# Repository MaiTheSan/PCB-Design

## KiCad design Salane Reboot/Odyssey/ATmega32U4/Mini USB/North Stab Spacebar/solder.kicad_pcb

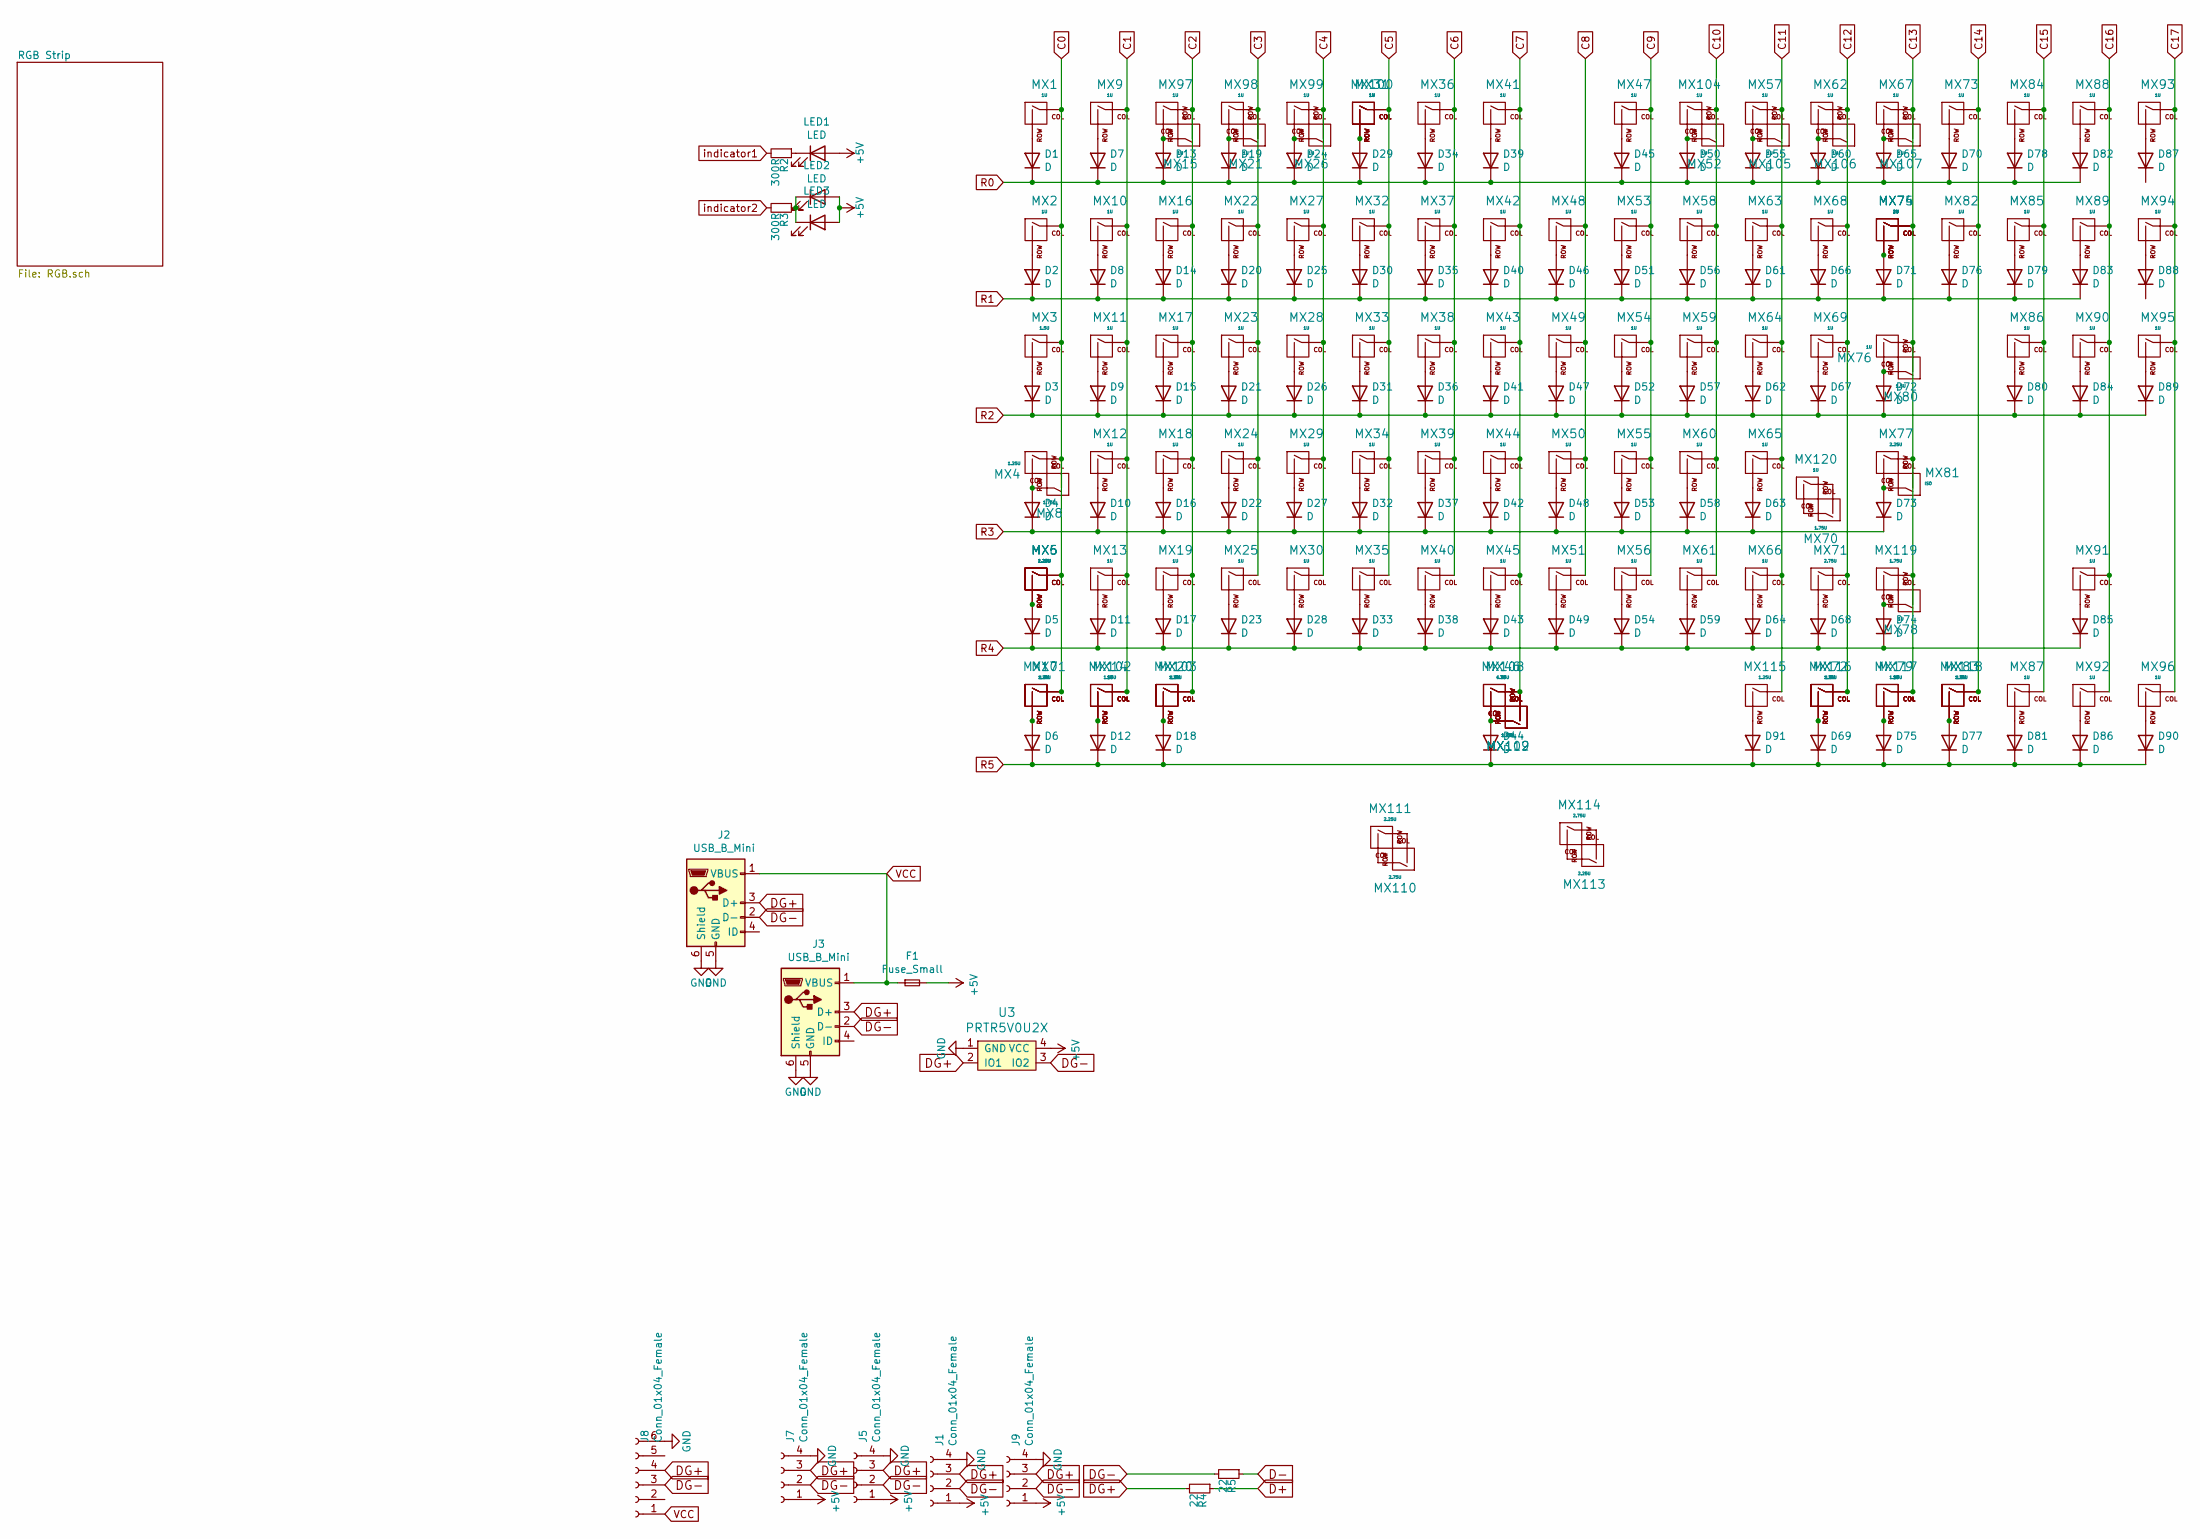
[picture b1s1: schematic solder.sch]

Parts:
D1, D2, D3, D4, D5, D6, D7, D8, D9, D10, D11, D12, D13, D14, D15, D16, D17, D18, D19, D20, D21, D22, D23, D24, D25, D26, D27, D28, D29, D30, D31, D32, D33, D34, D35, D36, D37, D38, D39, D40, D41, D42, D43, D44, D45, D46, D47, D48, D49, D50, D51, D52, D53, D54, D55, D56, D57, D58, D59, D60, D61, D62, D63, D64, D65, D66, D67, D68, D69, D70, D71, D72, D73, D74, D75, D76, D77, D78, D79, D80, D81, D82, D83, D84, D85, D86, D87, D88, D89, D90, D91: D; DIODE_1206_SawnsProjects
F1: Fuse_Small; Fuse_SMD1206_Reflow
J1, J7, J9: Conn_01x04_Female; JST-SR-4
J2, J3: USB_B_Mini; Molex-0548190589
J5: Conn_01x04_Female; PinHeader_1x04_P1.27mm_Vertical
J8: Conn_01x04_Female; BreakoutUSB
LED1, LED3: LED; MXOnly-LEDONLY-FLIPPED
LED2: LED; MXOnly-LEDONLY
MX1, MX2, MX9, MX10, MX11, MX12, MX13, MX14, MX15, MX16, MX17, MX18, MX19, MX21, MX22, MX23, MX24, MX25, MX26, MX27, MX28, MX29, MX30, MX31, MX32, MX33, MX34, MX35, MX36, MX37, MX38, MX39, MX40, MX41, MX42, MX43, MX44, MX45, MX47, MX48, MX49, MX50, MX51, MX52, MX53, MX54, MX55, MX56, MX57, MX58, MX59, MX60, MX61, MX62, MX63, MX64, MX65, MX66, MX67, MX68, MX69, MX73, MX74, MX76, MX78, MX79, MX82, MX84, MX85, MX86, MX87, MX88, MX89, MX90, MX91, MX92, MX93, MX94, MX95, MX96, MX97, MX98, MX99, MX100, MX104, MX105, MX106, MX107, MX120: 1U; MXOnly-1U-NoLED
MX3, MX7, MX20, MX72, MX80, MX83: 1.5U; MXOnly-1.5U-NoLED
MX4, MX5, MX101, MX102, MX103, MX109, MX112, MX115, MX116, MX117, MX118: 1.25U; MXOnly-1.25U-NoLED
MX6: 2.25U; MXOnly-2.25U-NoLED
MX8, MX70, MX119: 1.75U; MXOnly-1.75U-NoLED
MX46: 7U; MXOnly-7U-ReversedStabilizers-NoLED
MX71: 2.75U; MXOnly-2.75U-NoLED
MX75: 2U; MXOnly-2U-NoLED
MX77, MX111, MX113: 2.25U; MXOnly-2.25U-ReversedStabilizers-NoLED
MX81: ISO; MXOnly-ISO-ROTATED-ReversedStabilizers-NoLED
MX108: 6.25U; MXOnly-6.25U-ReversedStabilizers-NoLED
MX110, MX114: 2.75U; MXOnly-2.75U-ReversedStabilizers-NoLED
R2, R3: 300R; R_0805
R4, R5: 22; R_0805
U3: PRTR5V0U2X; SOT143B

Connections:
+5V: F1.2, J1.1, J5.1, J7.1, J9.1, LED1.2 (A), LED2.2 (A), LED3.2 (A), U3.4 (VCC)
C0: MX1.1 (COL), MX2.1 (COL), MX3.1 (COL), MX4.1 (COL), MX5.1 (COL), MX6.1 (COL), MX7.1 (COL), MX8.2 (ROW), MX101.1 (COL)
C1: MX9.1 (COL), MX10.1 (COL), MX11.1 (COL), MX12.1 (COL), MX13.1 (COL), MX14.1 (COL), MX102.1 (COL)
C2: MX15.2 (ROW), MX16.1 (COL), MX17.1 (COL), MX18.1 (COL), MX19.1 (COL), MX20.1 (COL), MX97.1 (COL), MX103.1 (COL)
C3: MX21.2 (ROW), MX22.1 (COL), MX23.1 (COL), MX24.1 (COL), MX25.1 (COL), MX98.1 (COL)
C4: MX26.2 (ROW), MX27.1 (COL), MX28.1 (COL), MX29.1 (COL), MX30.1 (COL), MX99.1 (COL)
C5: MX31.1 (COL), MX32.1 (COL), MX33.1 (COL), MX34.1 (COL), MX35.1 (COL), MX100.1 (COL)
C6: MX36.1 (COL), MX37.1 (COL), MX38.1 (COL), MX39.1 (COL), MX40.1 (COL)
C7: MX41.1 (COL), MX42.1 (COL), MX43.1 (COL), MX44.1 (COL), MX45.1 (COL), MX46.1 (COL), MX108.1 (COL), MX109.2 (ROW), MX112.2 (ROW)
C8: MX48.1 (COL), MX49.1 (COL), MX50.1 (COL), MX51.1 (COL)
C9: MX47.1 (COL), MX53.1 (COL), MX54.1 (COL), MX55.1 (COL), MX56.1 (COL)
C10: MX52.2 (ROW), MX58.1 (COL), MX59.1 (COL), MX60.1 (COL), MX61.1 (COL), MX104.1 (COL)
C11: MX57.1 (COL), MX63.1 (COL), MX64.1 (COL), MX65.1 (COL), MX66.1 (COL), MX105.2 (ROW), MX115.1 (COL)
C12: MX62.1 (COL), MX68.1 (COL), MX69.1 (COL), MX71.1 (COL), MX72.1 (COL), MX106.2 (ROW), MX116.1 (COL)
C13: MX67.1 (COL), MX74.1 (COL), MX75.1 (COL), MX76.1 (COL), MX77.1 (COL), MX78.2 (ROW), MX79.1 (COL), MX80.2 (ROW), MX81.2 (ROW), MX107.2 (ROW), MX117.1 (COL), MX119.1 (COL)
C14: MX73.1 (COL), MX82.1 (COL), MX83.1 (COL), MX118.1 (COL)
C15: MX84.1 (COL), MX85.1 (COL), MX86.1 (COL), MX87.1 (COL)
C16: MX88.1 (COL), MX89.1 (COL), MX90.1 (COL), MX91.1 (COL), MX92.1 (COL)
C17: MX93.1 (COL), MX94.1 (COL), MX95.1 (COL), MX96.1 (COL)
D+: R4.1
D-: R5.1
DG+: J1.3, J2.3 (D+), J3.3 (D+), J5.3, J7.3, J8.4, J9.3, R4.2, U3.2 (IO1)
DG-: J1.2, J2.2 (D-), J3.2 (D-), J5.2, J7.2, J8.3, J9.2, R5.2, U3.3 (IO2)
GND: J1.4, J2.5 (GND), J2.6 (Shield), J3.5 (GND), J3.6 (Shield), J5.4, J7.4, J8.6, J9.4, U3.1 (GND)
unnamed: D1.2 (A), MX1.2 (ROW)
unnamed: D2.2 (A), MX2.2 (ROW)
unnamed: D3.2 (A), MX3.2 (ROW)
unnamed: D4.2 (A), MX4.2 (ROW), MX8.1 (COL)
unnamed: D5.2 (A), MX5.2 (ROW), MX6.2 (ROW)
unnamed: D6.2 (A), MX7.2 (ROW), MX101.2 (ROW)
unnamed: D7.2 (A), MX9.2 (ROW)
unnamed: D8.2 (A), MX10.2 (ROW)
unnamed: D9.2 (A), MX11.2 (ROW)
unnamed: D10.2 (A), MX12.2 (ROW)
unnamed: D11.2 (A), MX13.2 (ROW)
unnamed: D12.2 (A), MX14.2 (ROW), MX102.2 (ROW)
unnamed: D13.2 (A), MX15.1 (COL), MX97.2 (ROW)
unnamed: D14.2 (A), MX16.2 (ROW)
unnamed: D15.2 (A), MX17.2 (ROW)
unnamed: D16.2 (A), MX18.2 (ROW)
unnamed: D17.2 (A), MX19.2 (ROW)
unnamed: D18.2 (A), MX20.2 (ROW), MX103.2 (ROW)
unnamed: D19.2 (A), MX21.1 (COL), MX98.2 (ROW)
unnamed: D20.2 (A), MX22.2 (ROW)
unnamed: D21.2 (A), MX23.2 (ROW)
unnamed: D22.2 (A), MX24.2 (ROW)
unnamed: D23.2 (A), MX25.2 (ROW)
unnamed: D24.2 (A), MX26.1 (COL), MX99.2 (ROW)
unnamed: D25.2 (A), MX27.2 (ROW)
unnamed: D26.2 (A), MX28.2 (ROW)
unnamed: D27.2 (A), MX29.2 (ROW)
unnamed: D28.2 (A), MX30.2 (ROW)
unnamed: D29.2 (A), MX31.2 (ROW), MX100.2 (ROW)
unnamed: D30.2 (A), MX32.2 (ROW)
unnamed: D31.2 (A), MX33.2 (ROW)
unnamed: D32.2 (A), MX34.2 (ROW)
unnamed: D33.2 (A), MX35.2 (ROW)
unnamed: D34.2 (A), MX36.2 (ROW)
unnamed: D35.2 (A), MX37.2 (ROW)
unnamed: D36.2 (A), MX38.2 (ROW)
unnamed: D37.2 (A), MX39.2 (ROW)
unnamed: D38.2 (A), MX40.2 (ROW)
unnamed: D39.2 (A), MX41.2 (ROW)
unnamed: D40.2 (A), MX42.2 (ROW)
unnamed: D41.2 (A), MX43.2 (ROW)
unnamed: D42.2 (A), MX44.2 (ROW)
unnamed: D43.2 (A), MX45.2 (ROW)
unnamed: D44.2 (A), MX46.2 (ROW), MX108.2 (ROW), MX109.1 (COL), MX112.1 (COL)
unnamed: D45.2 (A), MX47.2 (ROW)
unnamed: D46.2 (A), MX48.2 (ROW)
unnamed: D47.2 (A), MX49.2 (ROW)
unnamed: D48.2 (A), MX50.2 (ROW)
unnamed: D49.2 (A), MX51.2 (ROW)
unnamed: D50.2 (A), MX52.1 (COL), MX104.2 (ROW)
unnamed: D51.2 (A), MX53.2 (ROW)
unnamed: D52.2 (A), MX54.2 (ROW)
unnamed: D53.2 (A), MX55.2 (ROW)
unnamed: D54.2 (A), MX56.2 (ROW)
unnamed: D55.2 (A), MX57.2 (ROW), MX105.1 (COL)
unnamed: D56.2 (A), MX58.2 (ROW)
unnamed: D57.2 (A), MX59.2 (ROW)
unnamed: D58.2 (A), MX60.2 (ROW)
unnamed: D59.2 (A), MX61.2 (ROW)
unnamed: D60.2 (A), MX62.2 (ROW), MX106.1 (COL)
unnamed: D61.2 (A), MX63.2 (ROW)
unnamed: D62.2 (A), MX64.2 (ROW)
unnamed: D63.2 (A), MX65.2 (ROW)
unnamed: D64.2 (A), MX66.2 (ROW)
unnamed: D65.2 (A), MX67.2 (ROW), MX107.1 (COL)
unnamed: D66.2 (A), MX68.2 (ROW)
unnamed: D67.2 (A), MX69.2 (ROW)
unnamed: D68.2 (A), MX71.2 (ROW)
unnamed: D69.2 (A), MX72.2 (ROW), MX116.2 (ROW)
unnamed: D70.2 (A), MX73.2 (ROW)
unnamed: D71.2 (A), MX74.2 (ROW), MX75.2 (ROW)
unnamed: D72.2 (A), MX76.2 (ROW), MX80.1 (COL)
unnamed: D73.2 (A), MX77.2 (ROW), MX81.1 (COL)
unnamed: D74.2 (A), MX78.1 (COL), MX119.2 (ROW)
unnamed: D75.2 (A), MX79.2 (ROW), MX117.2 (ROW)
unnamed: D76.2 (A), MX82.2 (ROW)
unnamed: D77.2 (A), MX83.2 (ROW), MX118.2 (ROW)
unnamed: D78.2 (A), MX84.2 (ROW)
unnamed: D79.2 (A), MX85.2 (ROW)
unnamed: D80.2 (A), MX86.2 (ROW)
unnamed: D81.2 (A), MX87.2 (ROW)
unnamed: D82.2 (A), MX88.2 (ROW)
unnamed: D83.2 (A), MX89.2 (ROW)
unnamed: D84.2 (A), MX90.2 (ROW)
unnamed: D85.2 (A), MX91.2 (ROW)
unnamed: D86.2 (A), MX92.2 (ROW)
unnamed: D87.2 (A), MX93.2 (ROW)
unnamed: D88.2 (A), MX94.2 (ROW)
unnamed: D89.2 (A), MX95.2 (ROW)
unnamed: D90.2 (A), MX96.2 (ROW)
unnamed: D91.2 (A), MX115.2 (ROW)
unnamed: LED1.1 (K), R2.1
unnamed: LED2.1 (K), LED3.1 (K), R3.1
unnamed: MX110.1 (COL), MX111.2 (ROW)
unnamed: MX110.2 (ROW), MX111.1 (COL)
unnamed: MX113.1 (COL), MX114.2 (ROW)
unnamed: MX113.2 (ROW), MX114.1 (COL)
unnamed: MX70.2 (ROW), MX120.1 (COL)
unnamed: MX70.1 (COL), MX120.2 (ROW)
R0: D1.1 (K), D7.1 (K), D13.1 (K), D19.1 (K), D24.1 (K), D29.1 (K), D34.1 (K), D39.1 (K), D45.1 (K), D50.1 (K), D55.1 (K), D60.1 (K), D65.1 (K), D70.1 (K), D78.1 (K), D82.1 (K)
R1: D2.1 (K), D8.1 (K), D14.1 (K), D20.1 (K), D25.1 (K), D30.1 (K), D35.1 (K), D40.1 (K), D46.1 (K), D51.1 (K), D56.1 (K), D61.1 (K), D66.1 (K), D71.1 (K), D76.1 (K), D79.1 (K), D83.1 (K)
R2: D3.1 (K), D9.1 (K), D15.1 (K), D21.1 (K), D26.1 (K), D31.1 (K), D36.1 (K), D41.1 (K), D47.1 (K), D52.1 (K), D57.1 (K), D62.1 (K), D67.1 (K), D72.1 (K), D80.1 (K), D84.1 (K), D89.1 (K)
R3: D4.1 (K), D10.1 (K), D16.1 (K), D22.1 (K), D27.1 (K), D32.1 (K), D37.1 (K), D42.1 (K), D48.1 (K), D53.1 (K), D58.1 (K), D63.1 (K), D73.1 (K)
R4: D5.1 (K), D11.1 (K), D17.1 (K), D23.1 (K), D28.1 (K), D33.1 (K), D38.1 (K), D43.1 (K), D49.1 (K), D54.1 (K), D59.1 (K), D64.1 (K), D68.1 (K), D74.1 (K), D85.1 (K)
R5: D6.1 (K), D12.1 (K), D18.1 (K), D44.1 (K), D69.1 (K), D75.1 (K), D77.1 (K), D81.1 (K), D86.1 (K), D90.1 (K), D91.1 (K)
VCC: F1.1, J2.1 (VBUS), J3.1 (VBUS), J8.1
indicator1: R2.2
indicator2: R3.2

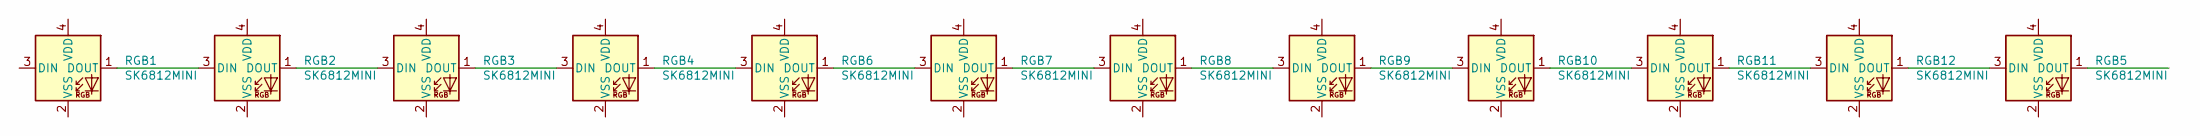
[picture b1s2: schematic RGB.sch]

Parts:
RGB1, RGB2, RGB3, RGB4, RGB5, RGB6, RGB7, RGB8, RGB9, RGB10, RGB11, RGB12: SK6812MINI; LED_WS2812B_PLCC4_5.0x5.0mm_P3.2mm

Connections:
unnamed: RGB1.1 (DOUT), RGB2.3 (DIN)
unnamed: RGB2.1 (DOUT), RGB3.3 (DIN)
unnamed: RGB3.1 (DOUT), RGB4.3 (DIN)
unnamed: RGB4.1 (DOUT), RGB6.3 (DIN)
unnamed: RGB6.1 (DOUT), RGB7.3 (DIN)
unnamed: RGB7.1 (DOUT), RGB8.3 (DIN)
unnamed: RGB8.1 (DOUT), RGB9.3 (DIN)
unnamed: RGB10.1 (DOUT), RGB11.3 (DIN)
unnamed: RGB9.1 (DOUT), RGB10.3 (DIN)
unnamed: RGB11.1 (DOUT), RGB12.3 (DIN)
unnamed: RGB5.3 (DIN), RGB12.1 (DOUT)

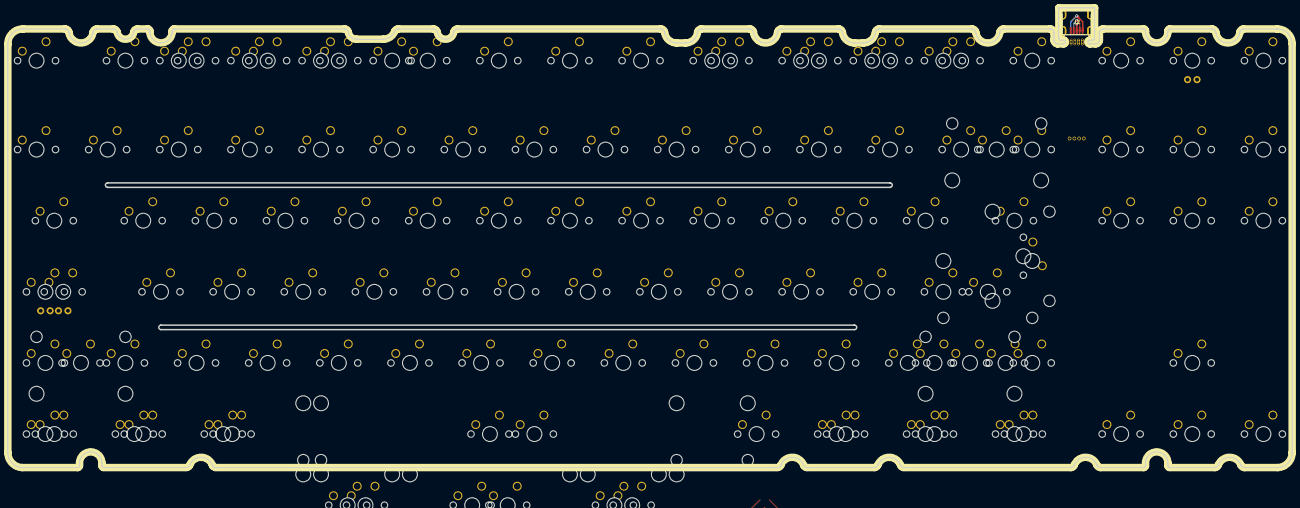
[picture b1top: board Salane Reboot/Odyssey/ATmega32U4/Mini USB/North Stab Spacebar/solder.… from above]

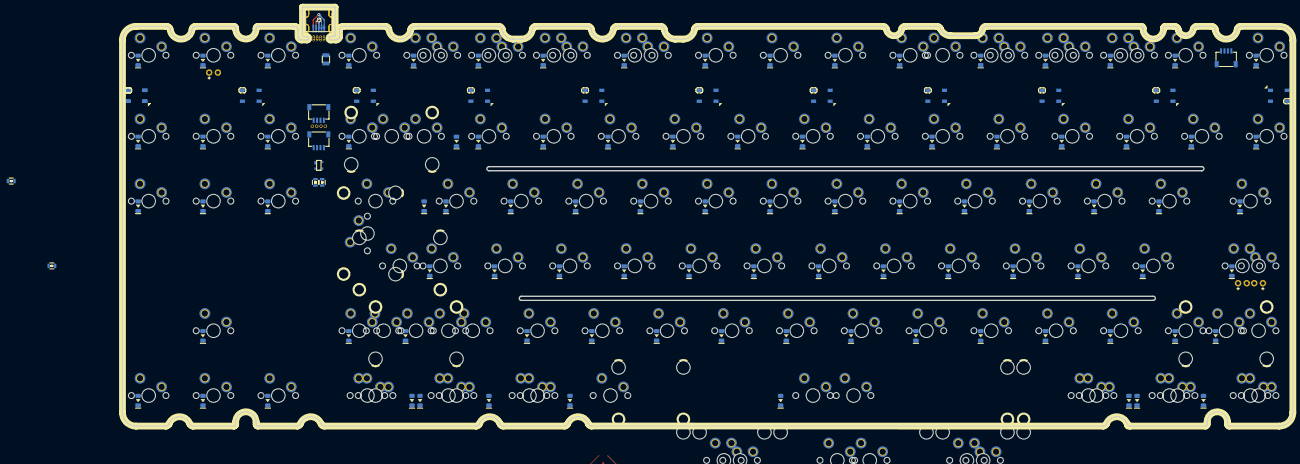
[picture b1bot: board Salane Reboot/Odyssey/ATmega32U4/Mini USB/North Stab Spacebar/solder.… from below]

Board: 2 copper layers, 344.0 x 123.1 mm, 239 parts (113 on the bottom side), 139 nets.

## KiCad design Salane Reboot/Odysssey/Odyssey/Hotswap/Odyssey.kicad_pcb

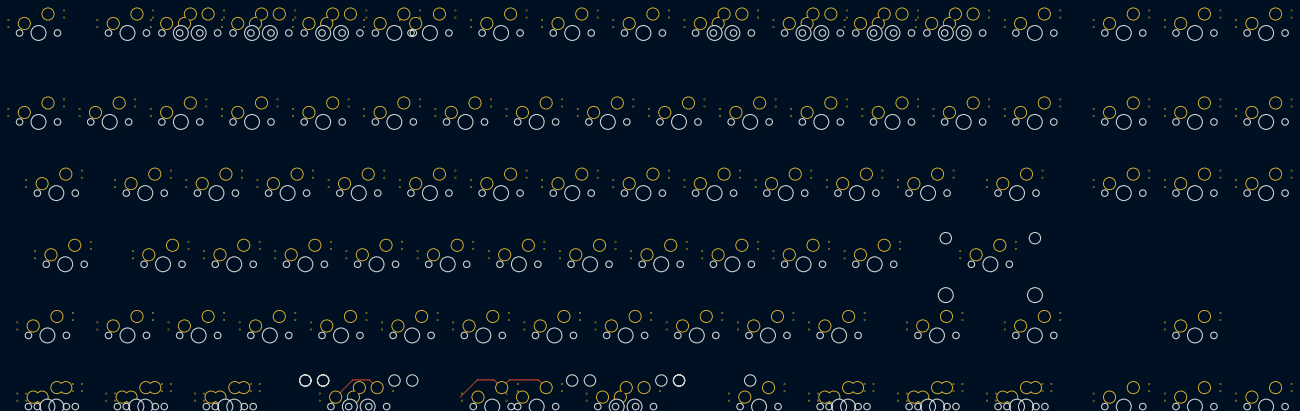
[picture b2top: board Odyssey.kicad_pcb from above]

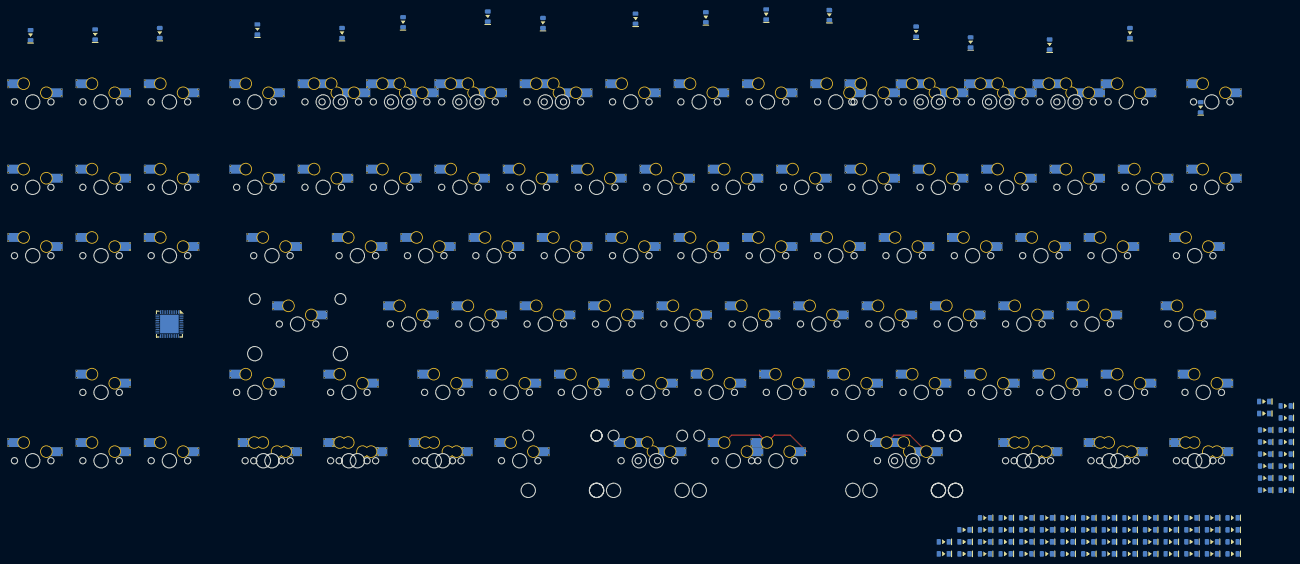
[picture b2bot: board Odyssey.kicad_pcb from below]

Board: 2 copper layers, 201 parts (91 on the bottom side), 108 nets.

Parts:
D1, D2, D3, D4, D5, D6, D7, D8, D9, D10, D11, D12, D13, D14, D15, D16, D17, D18, D19, D20, D21, D22, D23, D24, D25, D26, D27, D28, D29, D30, D31, D32, D33, D34, D35, D36, D37, D38, D39, D40, D41, D42, D43, D44, D45, D46, D47, D48, D49, D50, D51, D52, D53, D54, D55, D56, D57, D58, D59, D60, D61, D62, D63, D64, D65, D66, D67, D68, D69, D70, D71, D72, D73, D74, D75, D76, D77, D78, D79, D80, D81, D82, D83, D91, D92, D93, D94, D95, D96, D97: 1N4148W; DIODE_1206_SawnsProjects
MX1, MX2, MX3, MX4, MX5, MX6, MX7, MX8, MX9, MX10, MX11, MX12, MX13, MX14, MX15, MX16, MX17, MX18, MX19, MX20, MX21, MX22, MX23, MX24, MX25, MX26, MX27, MX28, MX29, MX30, MX31, MX32, MX33, MX34, MX36, MX37, MX38, MX39, MX40, MX41, MX42, MX43, MX44, MX45, MX46, MX47, MX49, MX50, MX51, MX53, MX54, MX55, MX56, MX57, MX58, MX59, MX60, MX61, MX62, MX63, MX65, MX67, MX68, MX69, MX70, MX71, MX72, MX73, MX74, MX75, MX76, MX77, MX78, MX91, MX95, MX96, MX97, MX99, MX102, MX114, MX115, MX116, MX117, MX118, MX119, MX120, MX121: 1U; MXOnly-1U-Hotswap-Sawns
MX35, MX48, MX98, MX100, MX101, MX103: 1.5U; MXOnly-1.5U-Hotswap-Sawns
MX52, MX79: 1.75U; MXOnly-1.75U-Hotswap-Sawns
MX64, MX83, MX86: 2.25U; MXOnly-2.25U-Hotswap-Sawns
MX66, MX80, MX81, MX82, MX85, MX92, MX93, MX94: 1.25U; MXOnly-1.25U-Hotswap-Sawns
MX84, MX87: 2.75U; MXOnly-2.75U-Hotswap-Sawns
MX90: 6.25U; MXOnly-6.25U-Hotswap-Sawns
MX104: 7U; MXOnly-7U-Hotswap-Sawns
U1: ATmega32U4-MU; QFN-44-1EP_7x7mm_P0.5mm_EP5.2x5.2mm

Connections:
unnamed: D1.2, MX1.2
unnamed: D2.2, MX2.2
unnamed: D3.2, MX3.2, MX114.1
unnamed: D4.2, MX4.2, MX115.1
unnamed: D5.2, MX5.2, MX116.1
unnamed: D6.2, MX6.2, MX117.1
unnamed: D7.2, MX7.2
unnamed: D8.2, MX8.2
unnamed: D9.2, MX9.2
unnamed: D10.2, MX10.2, MX118.1
unnamed: D11.2, MX11.2, MX119.1
unnamed: D12.2, MX12.2, MX120.1
unnamed: D13.2, MX13.2, MX121.1
unnamed: D14.2, MX14.2
unnamed: D15.2, MX15.2
unnamed: D16.2, MX16.2
unnamed: D17.2, MX17.2
unnamed: D18.2, MX18.2
unnamed: D19.2, MX19.2
unnamed: D20.2, MX20.2
unnamed: D21.2, MX21.2
unnamed: D22.2, MX22.2
unnamed: D23.2, MX23.2
unnamed: D24.2, MX24.2
unnamed: D25.2, MX25.2
unnamed: D26.2, MX26.2
unnamed: D27.2, MX27.2
unnamed: D28.2, MX28.2
unnamed: D29.2, MX29.2
unnamed: D30.2, MX30.2
unnamed: D31.2, MX31.2
unnamed: D32.2, MX32.2
unnamed: D33.2, MX33.2
unnamed: D34.2, MX34.2
unnamed: D35.2, MX35.2
unnamed: D36.2, MX36.2
unnamed: D37.2, MX37.2
unnamed: D38.2, MX38.2
unnamed: D39.2, MX39.2
unnamed: D40.2, MX40.2
unnamed: D41.2, MX41.2
unnamed: D42.2, MX42.2
unnamed: D43.2, MX43.2
unnamed: D44.2, MX44.2
unnamed: D45.2, MX45.2
unnamed: D46.2, MX46.2
unnamed: D47.2, MX47.2
unnamed: D48.2, MX48.2
unnamed: D49.2, MX49.2
unnamed: D50.2, MX50.2
unnamed: D51.2, MX51.2
unnamed: D52.2, MX52.2
unnamed: D53.2, MX53.2
unnamed: D54.2, MX54.2
unnamed: D55.2, MX55.2
unnamed: D56.2, MX56.2
unnamed: D57.2, MX57.2
unnamed: D58.2, MX58.2
unnamed: D59.2, MX59.2
unnamed: D60.2, MX60.2
unnamed: D61.2, MX61.2
unnamed: D62.2, MX62.2
unnamed: D63.2, MX63.2
unnamed: D64.2, MX64.2
unnamed: D65.2, MX65.2
unnamed: D66.2, MX66.2
unnamed: D67.2, MX67.2
unnamed: D68.2, MX68.2
unnamed: D69.2, MX69.2
unnamed: D70.2, MX70.2
unnamed: D71.2, MX71.2
unnamed: D72.2, MX72.2
unnamed: D73.2, MX73.2
unnamed: D74.2, MX74.2
unnamed: D75.2, MX75.2
unnamed: D76.2, MX76.2
unnamed: D77.2, MX77.2
unnamed: D78.2, MX79.2
unnamed: D79.2, MX78.2
unnamed: D80.2, MX80.2, MX98.2
unnamed: D81.2, MX81.2, MX99.2
unnamed: D82.2, MX82.2, MX100.2
unnamed: D83.2, MX85.2
unnamed: D91.2, MX94.2, MX101.2
unnamed: D92.2, MX92.2, MX102.2
unnamed: D93.2, MX93.2, MX103.2
unnamed: D94.2, MX91.2
unnamed: D95.2, MX95.2
unnamed: D96.2, MX96.2
unnamed: D97.2, MX97.2
unnamed: MX1.1, MX2.1, MX18.1, MX19.1, MX35.1, MX36.1, MX52.1, MX53.1, MX66.1, MX67.1, MX80.1, MX81.1, MX98.1, MX99.1
unnamed: MX9.1, MX10.1, MX26.1, MX27.1, MX43.1, MX44.1, MX60.1, MX61.1, MX74.1, MX75.1, MX118.2
unnamed: MX15.1, MX16.1, MX32.1, MX33.1, MX49.1, MX50.1, MX91.1, MX95.1, MX96.1
unnamed: MX17.1, MX34.1, MX51.1
unnamed: MX7.1, MX8.1, MX24.1, MX25.1, MX41.1, MX42.1, MX58.1, MX59.1, MX72.1, MX73.1
unnamed: MX83.1, MX87.2
unnamed: MX83.2, MX87.1
unnamed: MX84.1, MX86.2
unnamed: MX84.2, MX86.1
unnamed: MX3.1, MX4.1, MX20.1, MX21.1, MX37.1, MX38.1, MX54.1, MX55.1, MX68.1, MX69.1, MX82.1, MX100.1, MX114.2, MX115.2
unnamed: MX11.1, MX12.1, MX28.1, MX29.1, MX45.1, MX46.1, MX62.1, MX63.1, MX76.1, MX77.1, MX85.1, MX94.1, MX101.1, MX119.2, MX120.2
unnamed: MX13.1, MX14.1, MX30.1, MX31.1, MX47.1, MX48.1, MX64.1, MX65.1, MX78.1, MX79.1, MX92.1, MX93.1, MX102.1, MX103.1, MX121.2
unnamed: MX90.1, MX104.1
unnamed: MX90.2, MX104.2
unnamed: MX5.1, MX6.1, MX22.1, MX23.1, MX39.1, MX40.1, MX56.1, MX57.1, MX70.1, MX71.1, MX116.2, MX117.2
unnamed: U1.14, U1.34
unnamed: U1.15, U1.23, U1.35, U1.43, U1.45
unnamed: U1.24, U1.44

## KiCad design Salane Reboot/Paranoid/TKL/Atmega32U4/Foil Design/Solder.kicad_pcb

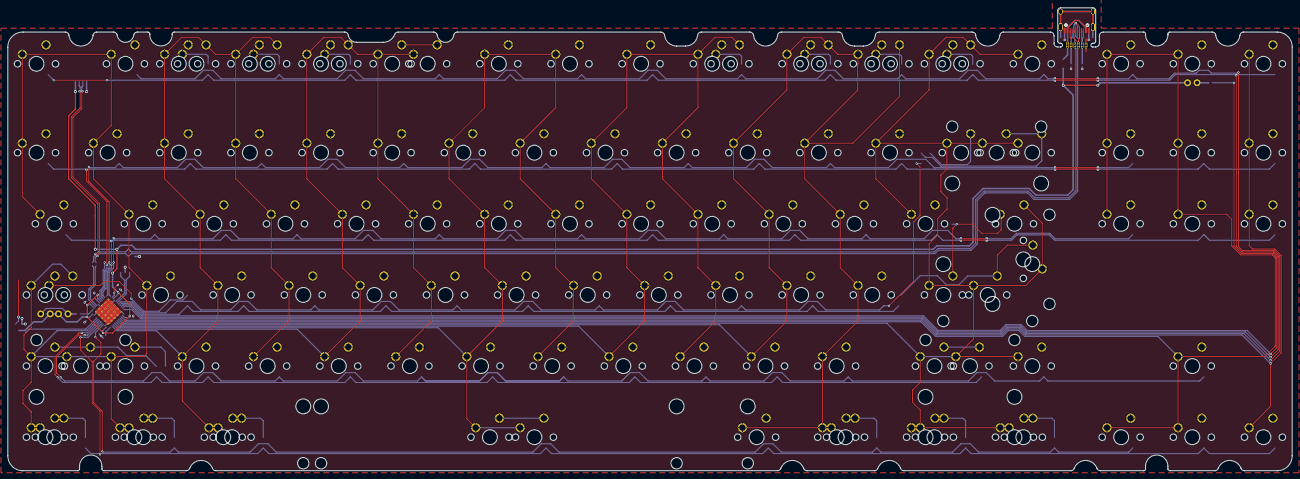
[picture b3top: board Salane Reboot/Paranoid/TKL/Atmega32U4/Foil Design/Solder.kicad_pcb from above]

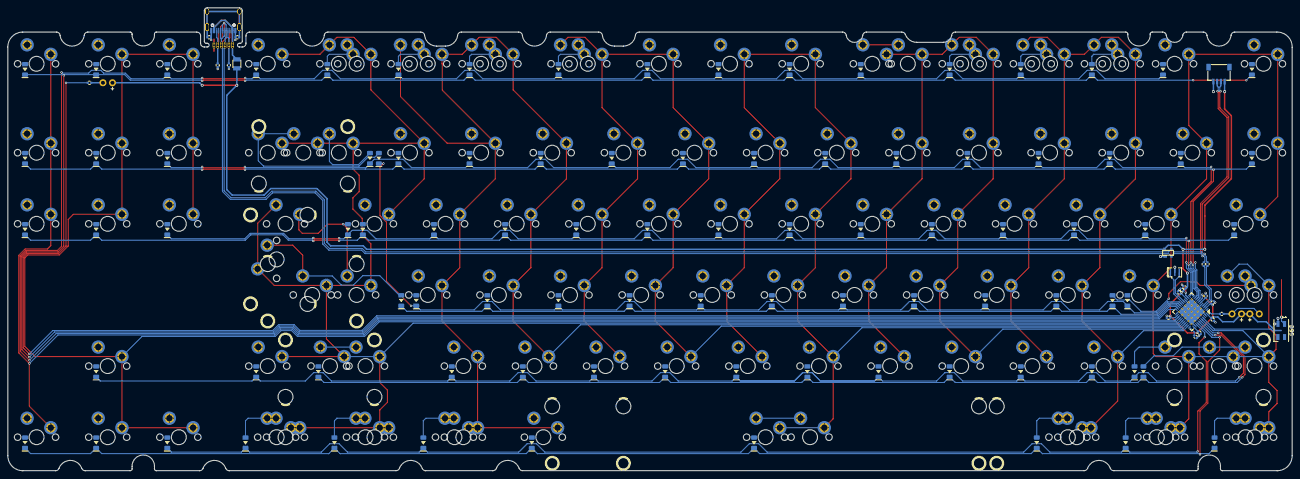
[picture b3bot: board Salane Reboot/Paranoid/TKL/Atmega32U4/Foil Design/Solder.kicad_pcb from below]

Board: 2 copper layers, 344.0 x 124.0 mm, 232 parts (115 on the bottom side), 131 nets.

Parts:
C1, C2, C3, C4, C6, C8: 0.1uF; C_0402
C5: 1uF; C_0402
C7: 10uF; C_0402
D1, D2, D3, D4, D5, D6, D7, D8, D9, D10, D11, D12, D13, D14, D15, D16, D17, D18, D19, D20, D21, D22, D23, D24, D25, D26, D27, D28, D29, D30, D31, D32, D33, D34, D35, D36, D37, D38, D39, D40, D41, D42, D43, D44, D45, D46, D47, D48, D49, D50, D51, D52, D53, D54, D55, D56, D57, D58, D59, D60, D61, D62, D63, D64, D65, D66, D67, D68, D69, D70, D71, D72, D73, D74, D75, D76, D77, D78, D79, D80, D81, D82, D83, D84, D85, D86, D87, D88, D89, D91, D92: 1N4148W; DIODE_1206_SawnsProjects
D90, D93: LED; MXOnly-LEDONLY
D94: LED; MXOnly-LEDONLY-FLIPPED
D95: SK6812MINI; LED_SK6812MINI_PLCC4_3.5x3.5mm_P1.75mm
F1: 500mA; Fuse_SMD1206_Reflow
J1: Conn_01x06_Female; BreakoutUSB
J2: Conn_01x04_Female; JST-SR-4
MX1, MX2, MX3, MX4, MX5, MX6, MX7, MX8, MX9, MX10, MX11, MX12, MX13, MX14, MX15, MX16, MX17, MX18, MX19, MX20, MX21, MX22, MX23, MX24, MX25, MX26, MX27, MX28, MX29, MX30, MX31, MX32, MX33, MX34, MX36, MX37, MX38, MX39, MX40, MX41, MX42, MX43, MX44, MX45, MX46, MX47, MX49, MX50, MX51, MX53, MX54, MX55, MX56, MX57, MX58, MX59, MX60, MX61, MX62, MX63, MX65, MX67, MX68, MX69, MX70, MX71, MX72, MX73, MX74, MX75, MX76, MX77, MX79, MX88, MX89, MX90, MX91, MX94, MX97, MX100, MX105, MX106, MX107, MX108, MX112, MX113, MX114, MX115: 1U; MXOnly-1U-NoLED
MX35, MX48, MX92, MX93, MX96, MX98: 1.5U; MXOnly-1.5U-NoLED
MX52, MX103: 1.75U; MXOnly-1.75U-NoLED
MX64: 2.25U; MXOnly-2.25U-ReversedStabilizers-NoLED
MX66, MX80, MX81, MX82, MX84, MX85, MX86, MX87, MX101: 1.25U; MXOnly-1.25U-NoLED
MX78: 2.75U; MXOnly-2.75U-NoLED
MX83: 6.25U; MXOnly-6.25U-ReversedStabilizers-NoLED
MX95: 7U; MXOnly-7U-ReversedStabilizers-NoLED
MX99: ISO; MXOnly-ISO-ROTATED-ReversedStabilizers-NoLED
MX102: 2.25U; MXOnly-2.25U-NoLED
MX104: 2U; MXOnly-2U-NoLED
R1, R2: 5.1k; R_0402
R3, R4: 10k; R_0402
R5, R6: 22R; R_0402
R7: 1M; R_0402
R8, R9: 300R; R_0402
U1: ATmega32U4-MU; QFN-44-1EP_7x7mm_P0.5mm_EP5.2x5.2mm
U2: PRTR5V0U2X; SOT143B
USB1, USB2: HRO-TYPE-C-31-M-12-Type-C; HRO-TYPE-C-31-M-12-Assembly
Y1: 16MHz; Resonator_SMD_muRata_CSTxExxV-3Pin_3.0x1.1mm

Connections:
+5V: C1.1, C2.1, C3.1, C4.1, C6.1, C7.1, D90.2, D93.2, D94.2, F1.2, J2.1, R3.1, U1.2, U1.7, U1.14, U1.24, U1.34, U1.44, U2.4
C0: MX1.1, MX2.1, MX18.1, MX19.1, MX35.1, MX36.1, MX52.2, MX53.1, MX66.1, MX67.1, MX80.1, MX81.1, MX92.1, MX94.1, MX101.1, MX102.1, U1.40
C1: MX3.2, MX4.2, MX20.1, MX21.1, MX37.1, MX38.1, MX54.1, MX55.1, MX68.1, MX69.1, MX82.1, MX93.1, MX105.1, MX106.1, U1.32
C2: MX5.2, MX6.1, MX22.1, MX23.1, MX39.1, MX40.1, MX56.1, MX57.1, MX70.1, MX71.1, MX107.1, MX108.1, U1.31
C3: MX7.1, MX8.1, MX24.1, MX25.1, MX41.1, MX42.1, MX58.1, MX59.1, MX72.1, MX73.1, MX83.1, MX95.1, U1.30
C4: MX9.1, MX10.2, MX26.1, MX27.1, MX43.1, MX44.1, MX60.1, MX61.1, MX74.1, MX75.1, MX112.1, U1.29
C5: MX11.1, MX12.1, MX28.1, MX29.1, MX45.1, MX46.1, MX62.1, MX63.1, MX76.1, MX77.1, MX84.1, MX85.1, MX96.1, MX113.2, MX114.2, U1.28
C6: MX13.1, MX14.1, MX30.1, MX31.1, MX47.1, MX48.2, MX64.1, MX65.1, MX78.1, MX79.1, MX86.1, MX87.1, MX97.1, MX98.1, MX99.2, MX100.1, MX103.1, MX104.1, MX115.2, U1.27
C7: MX15.1, MX16.1, MX32.1, MX33.1, MX49.1, MX50.1, MX88.1, MX89.1, MX90.1, U1.26
C8: MX17.1, MX34.1, MX51.1, MX91.1, U1.25
C+: J1.4, J2.3, R6.1, U2.2, USB1.6, USB1.8, USB2.6, USB2.8
C-: J1.3, J2.2, R5.2, U2.3, USB1.5, USB1.7, USB2.5, USB2.7
CC1: J1.2, R1.2, USB1.4, USB2.10
CC2: J1.5, R2.1, USB1.10, USB2.4
Caps: R8.1, U1.1
D+: R6.2, U1.4
D-: R5.1, U1.3
Fuse: F1.1, J1.1, USB1.2, USB1.11, USB2.2, USB2.11
GND: C1.2, C2.2, C3.2, C4.2, C5.1, C6.2, C7.2, C8.2, J1.6, J2.4, R1.1, R2.2, R4.1, R7.1, U1.5, U1.15, U1.23, U1.35, U1.43, U1.45, U2.1, USB1.1, USB1.12, USB2.1, USB2.12, Y1.2
unnamed: C5.2, U1.6
unnamed: D1.2, MX1.2
unnamed: D2.2, MX18.2
unnamed: D3.2, MX35.2
unnamed: D4.2, MX52.1, MX101.2
unnamed: D5.2, MX66.2, MX102.2
unnamed: D6.2, MX80.2, MX92.2
unnamed: D7.2, MX2.2
unnamed: D8.2, MX19.2
unnamed: D9.2, MX36.2
unnamed: D10.2, MX53.2
unnamed: D11.2, MX67.2
unnamed: D12.2, MX81.2, MX94.2
unnamed: D13.2, MX3.1, MX105.2
unnamed: D14.2, MX20.2
unnamed: D15.2, MX37.2
unnamed: D16.2, MX54.2
unnamed: D17.2, MX68.2
unnamed: D18.2, MX82.2, MX93.2
unnamed: D19.2, MX4.1, MX106.2
unnamed: D20.2, MX21.2
unnamed: D21.2, MX38.2
unnamed: D22.2, MX55.2
unnamed: D23.2, MX69.2
unnamed: D24.2, MX32.2
unnamed: D25.2, MX5.1, MX107.2
unnamed: D26.2, MX22.2
unnamed: D27.2, MX39.2
unnamed: D28.2, MX56.2
unnamed: D29.2, MX70.2
unnamed: D30.2, MX33.2
unnamed: D31.2, MX6.2, MX108.2
unnamed: D32.2, MX23.2
unnamed: D33.2, MX40.2
unnamed: D34.2, MX57.2
unnamed: D35.2, MX71.2
unnamed: D36.2, MX17.2
unnamed: D37.2, MX7.2
unnamed: D38.2, MX24.2
unnamed: D39.2, MX41.2
unnamed: D40.2, MX58.2
unnamed: D41.2, MX72.2
unnamed: D42.2, MX83.2, MX95.2
unnamed: D43.2, MX8.2
unnamed: D44.2, MX25.2
unnamed: D45.2, MX42.2
unnamed: D46.2, MX59.2
unnamed: D47.2, MX73.2
unnamed: D48.2, MX34.2
unnamed: D49.2, MX9.2
unnamed: D50.2, MX26.2
unnamed: D51.2, MX43.2
unnamed: D52.2, MX60.2
unnamed: D53.2, MX74.2
unnamed: D54.2, MX51.2
unnamed: D55.2, MX10.1, MX112.2
unnamed: D56.2, MX27.2
unnamed: D57.2, MX44.2
unnamed: D58.2, MX61.2
unnamed: D59.2, MX75.2
unnamed: D60.2, MX91.2
unnamed: D61.2, MX11.2, MX113.1
unnamed: D62.2, MX28.2
unnamed: D63.2, MX45.2
unnamed: D64.2, MX62.2
unnamed: D65.2, MX76.2
unnamed: D66.2, MX84.2
unnamed: D67.2, MX12.2, MX114.1
unnamed: D68.2, MX29.2
unnamed: D69.2, MX46.2
unnamed: D70.2, MX63.2
unnamed: D71.2, MX77.2
unnamed: D72.2, MX85.2, MX96.2
unnamed: D73.2, MX13.2, MX115.1
unnamed: D74.2, MX30.2
unnamed: D75.2, MX47.2
unnamed: D76.2, MX64.2, MX99.1
unnamed: D77.2, MX78.2, MX103.2
unnamed: D78.2, MX86.2, MX97.2
unnamed: D79.2, MX14.2
unnamed: D80.2, MX31.2
unnamed: D81.2, MX48.1, MX100.2
unnamed: D82.2, MX65.2, MX104.2
unnamed: D83.2, MX79.2
unnamed: D84.2, MX87.2, MX98.2
unnamed: D85.2, MX15.2
unnamed: D86.2, MX49.2
unnamed: D87.2, MX89.2
unnamed: D88.2, MX16.2
unnamed: D89.2, MX50.2
unnamed: D90.1, D94.1, R8.2
unnamed: D91.2, MX88.2
unnamed: D92.2, MX90.2
unnamed: D93.1, R9.2
unnamed: R3.2, U1.13
unnamed: R4.2, U1.33
unnamed: U1.16, Y1.3
unnamed: U1.17, Y1.1
R0: D1.1, D13.1, D25.1, D36.1, D37.1, D49.1, D61.1, D73.1, D88.1, U1.21
R1: D7.1, D19.1, D31.1, D43.1, D55.1, D67.1, D79.1, D85.1, U1.22
R2: D2.1, D14.1, D26.1, D30.1, D38.1, D48.1, D50.1, D62.1, D74.1, U1.9
R3: D8.1, D20.1, D24.1, D32.1, D44.1, D56.1, D68.1, D80.1, U1.10
R4: D3.1, D15.1, D27.1, D39.1, D51.1, D54.1, D63.1, D75.1, D89.1, U1.11
R5: D9.1, D21.1, D33.1, D45.1, D57.1, D69.1, D81.1, D86.1, U1.12
R6: D4.1, D16.1, D28.1, D40.1, D52.1, D64.1, D76.1, U1.19
R7: D10.1, D22.1, D34.1, D46.1, D58.1, D70.1, D82.1, U1.18
R8: D5.1, D17.1, D29.1, D41.1, D53.1, D65.1, D77.1, U1.39
R9: D11.1, D23.1, D35.1, D47.1, D59.1, D71.1, D83.1, D91.1, U1.38
R10: D6.1, D18.1, D42.1, D60.1, D66.1, D78.1, D92.1, U1.37
R11: D12.1, D72.1, D84.1, D87.1, U1.36
Scroll: R9.1, U1.20
Shiled: C8.1, R7.2, USB1.13, USB2.13
